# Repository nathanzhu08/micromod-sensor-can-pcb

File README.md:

# micromod-sensor-can-pcb
KiCad PCB design completed for the SJSU Robotics electrical trial project, featuring a 3.3V I²C temperature/humidity sensor, a MicroMod interface, and CAN bus communication.

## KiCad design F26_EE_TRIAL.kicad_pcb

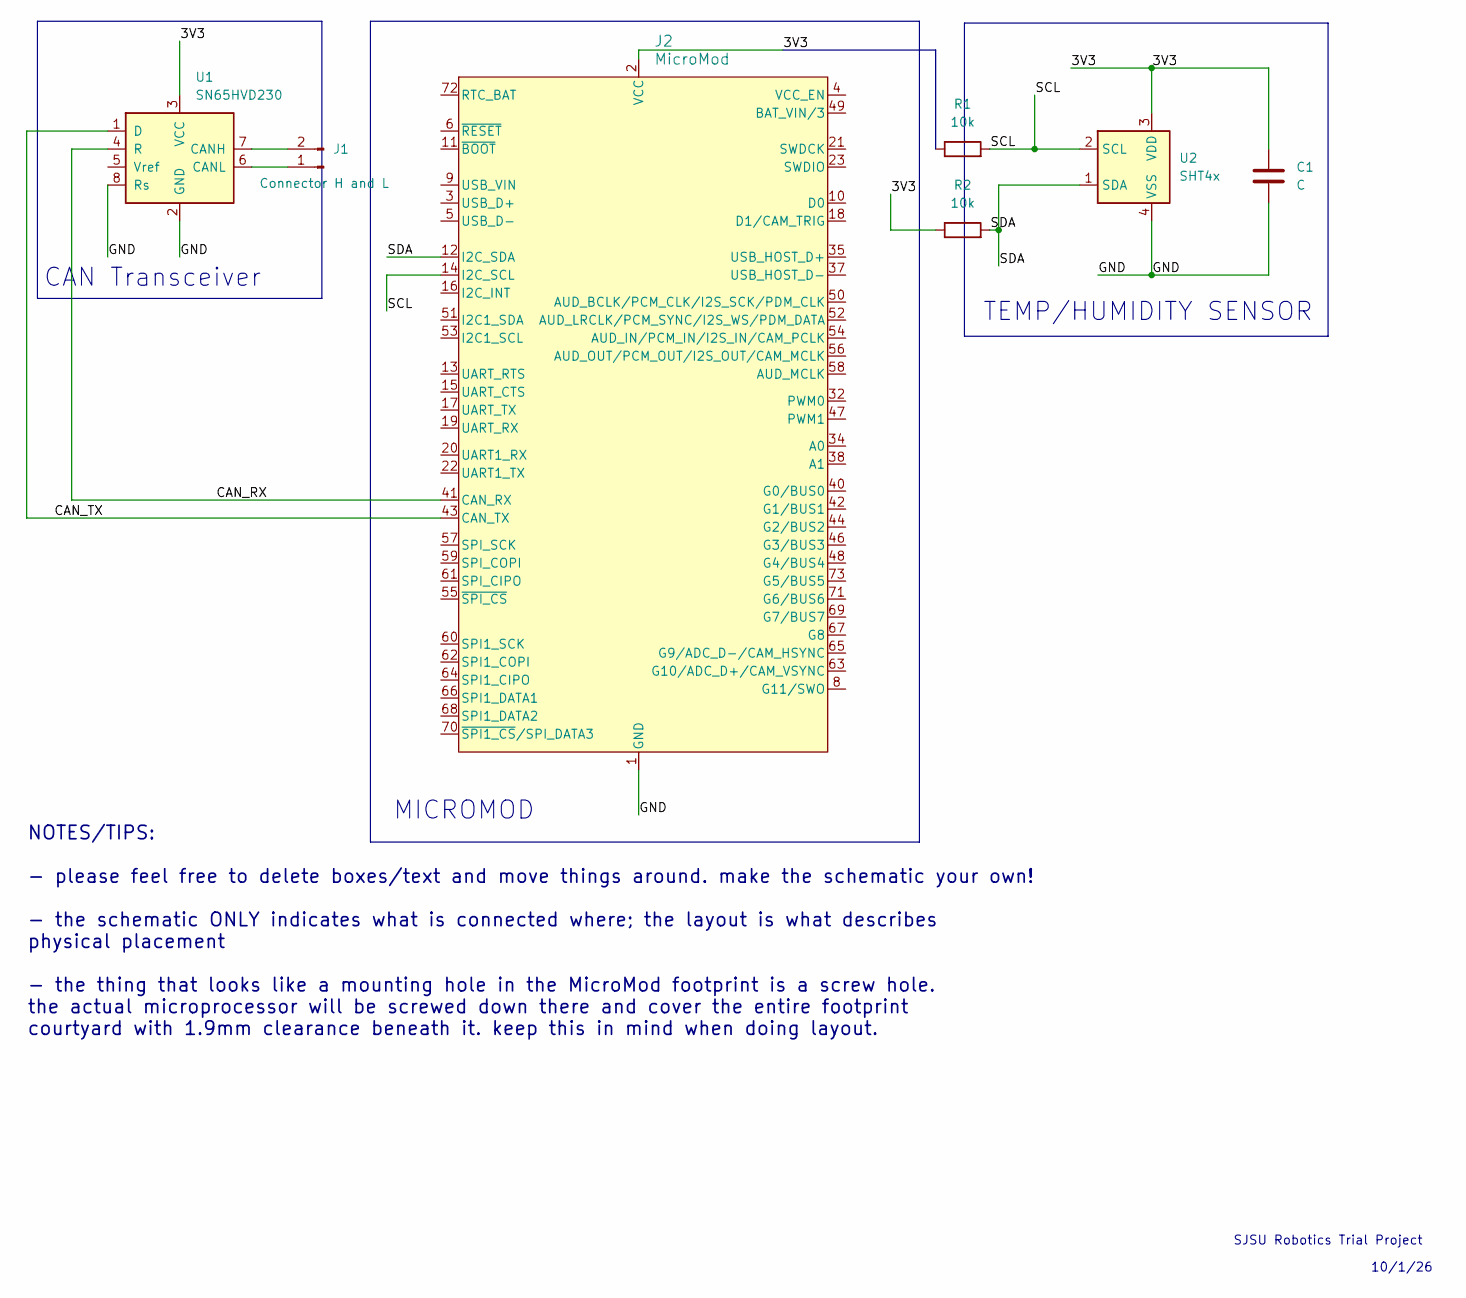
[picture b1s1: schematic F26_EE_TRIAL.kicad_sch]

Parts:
C1: C; C_0603_1608Metric
J1: Connector H and L; PinSocket_1x02_P2.54mm_Horizontal
J2: MicroMod; micromod
R1, R2: 10k; R_0603_1608Metric
U1: SN65HVD230; SOIC-8_3.9x4.9mm_P1.27mm
U2: SHT4x; Sensirion_DFN-4_1.5x1.5mm_P0.8mm_SHT4x_NoCentralPad

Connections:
/CAN_RX: J2.41 (CAN_RX), U1.4 (R)
/CAN_TX: J2.43 (CAN_TX), U1.1 (D)
/GND: C1.2, J2.1 (GND), J2.7 (GND), J2.33 (GND), J2.36 (GND), J2.39 (GND), J2.45 (GND), J2.75 (GND), J2.S1 (GND), J2.S2 (GND), J2.S3 (GND), U1.2 (GND), U1.8 (Rs), U2.4 (VSS)
/SCL: J2.14 (I2C_SCL), R1.2, U2.2 (SCL)
/SDA: J2.12 (I2C_SDA), R2.2, U2.1 (SDA)
unnamed: J1.1, U1.6 (CANL)
unnamed: J1.2, U1.7 (CANH)
VCC: C1.1, J2.2 (VCC), J2.74 (VCC), R1.1, R2.1, U1.3 (VCC), U2.3 (VDD)

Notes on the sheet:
10/1/26
CAN Transceiver
MICROMOD
SJSU Robotics Trial Project
NOTES/TIPS: - please feel free to delete boxes/text and move things around. make the schematic your own! - the schematic ONLY indicates what is connected where; the layout is what describes physical placement - the thing that looks like a mounting hole in the MicroMod footprint is a screw hole. the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
TEMP/HUMIDITY SENSOR

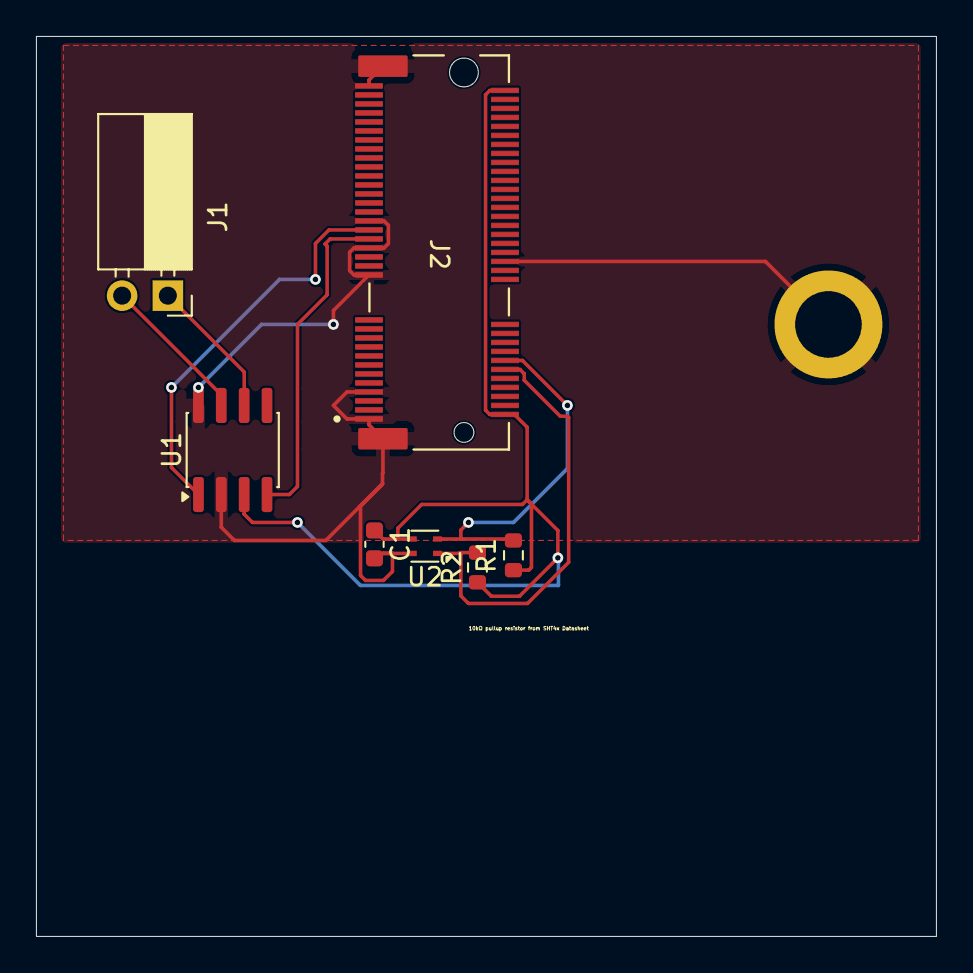
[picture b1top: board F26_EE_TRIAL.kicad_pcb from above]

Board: 2 copper layers, 50.0 x 50.0 mm, 7 parts (0 on the bottom side), 8 nets.
